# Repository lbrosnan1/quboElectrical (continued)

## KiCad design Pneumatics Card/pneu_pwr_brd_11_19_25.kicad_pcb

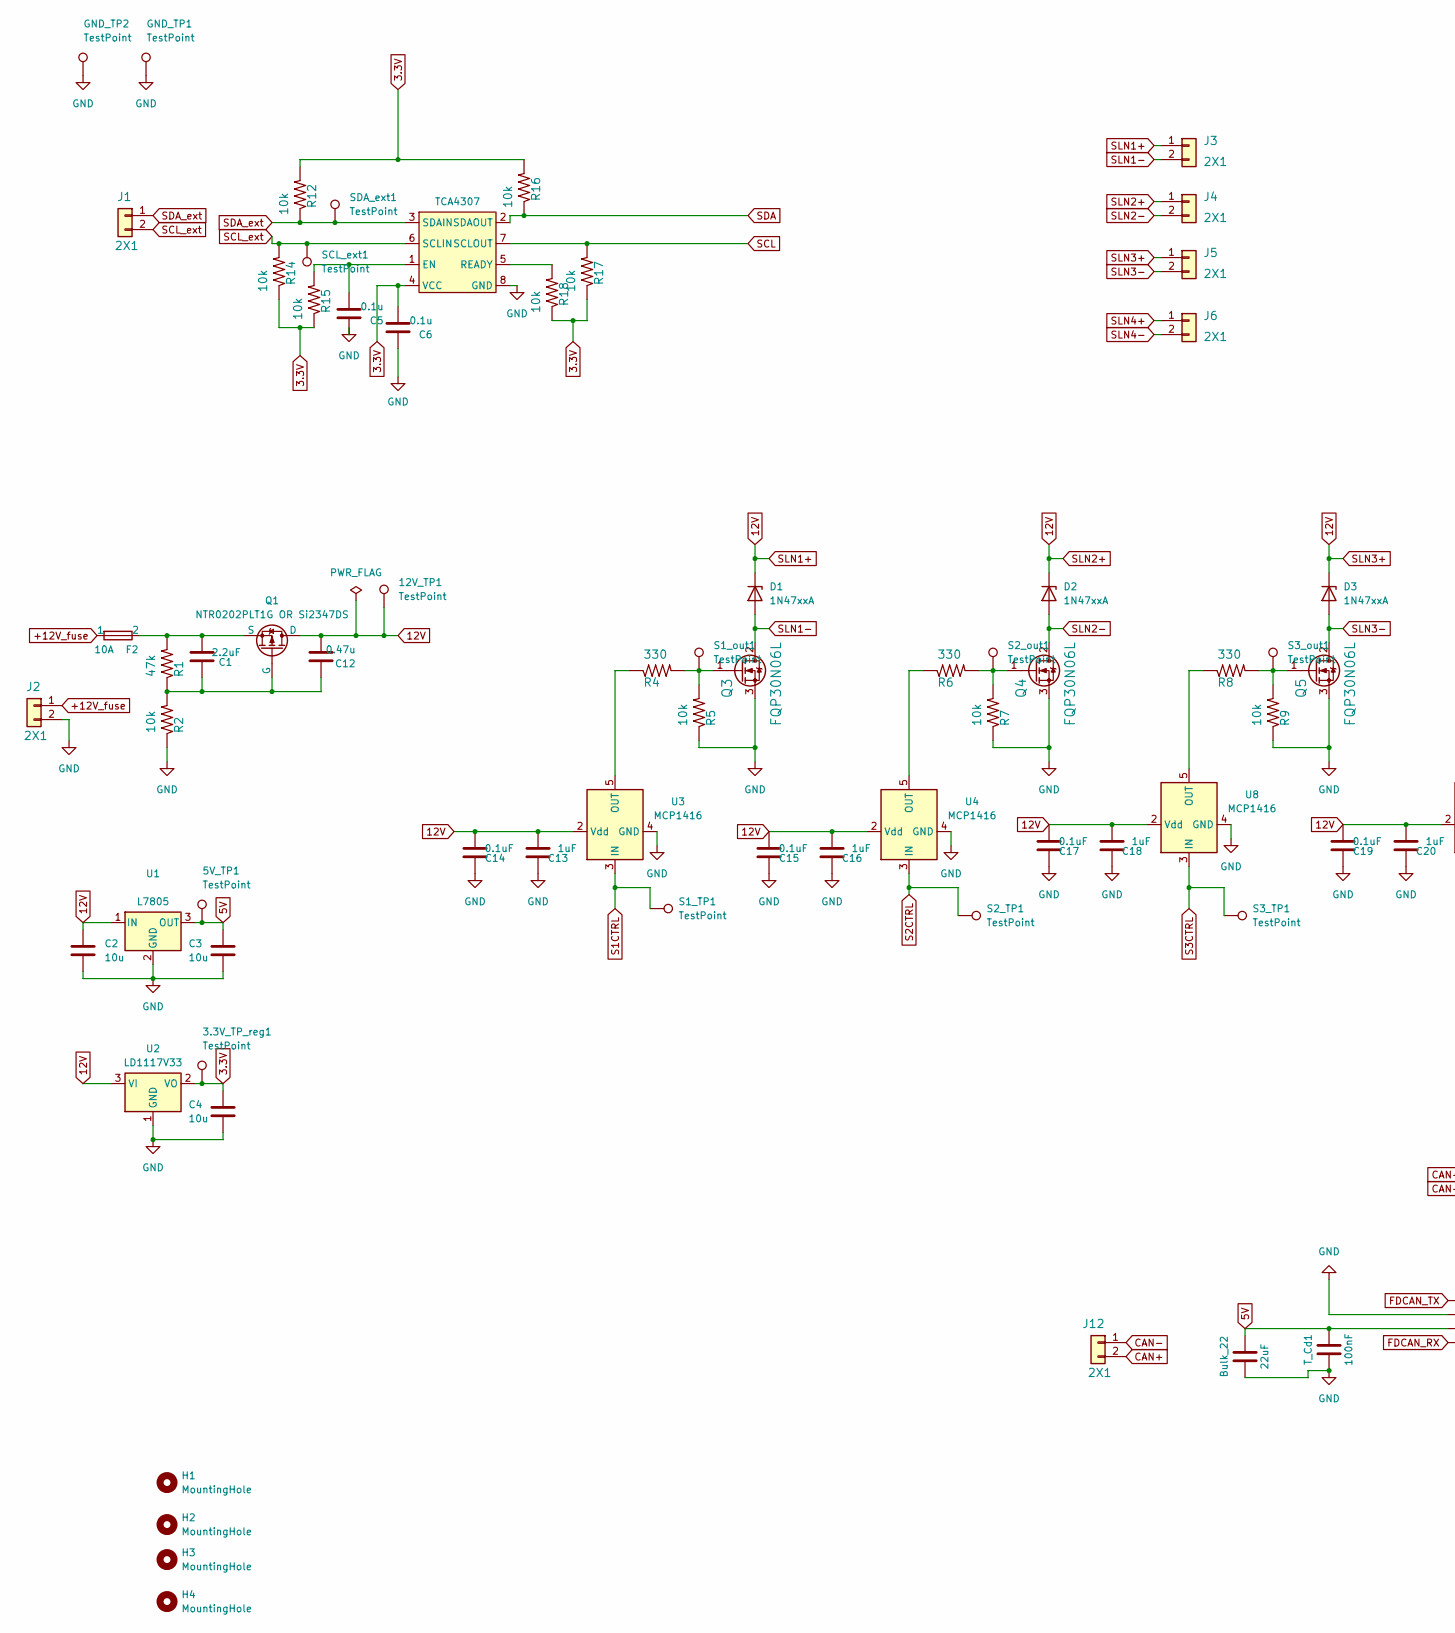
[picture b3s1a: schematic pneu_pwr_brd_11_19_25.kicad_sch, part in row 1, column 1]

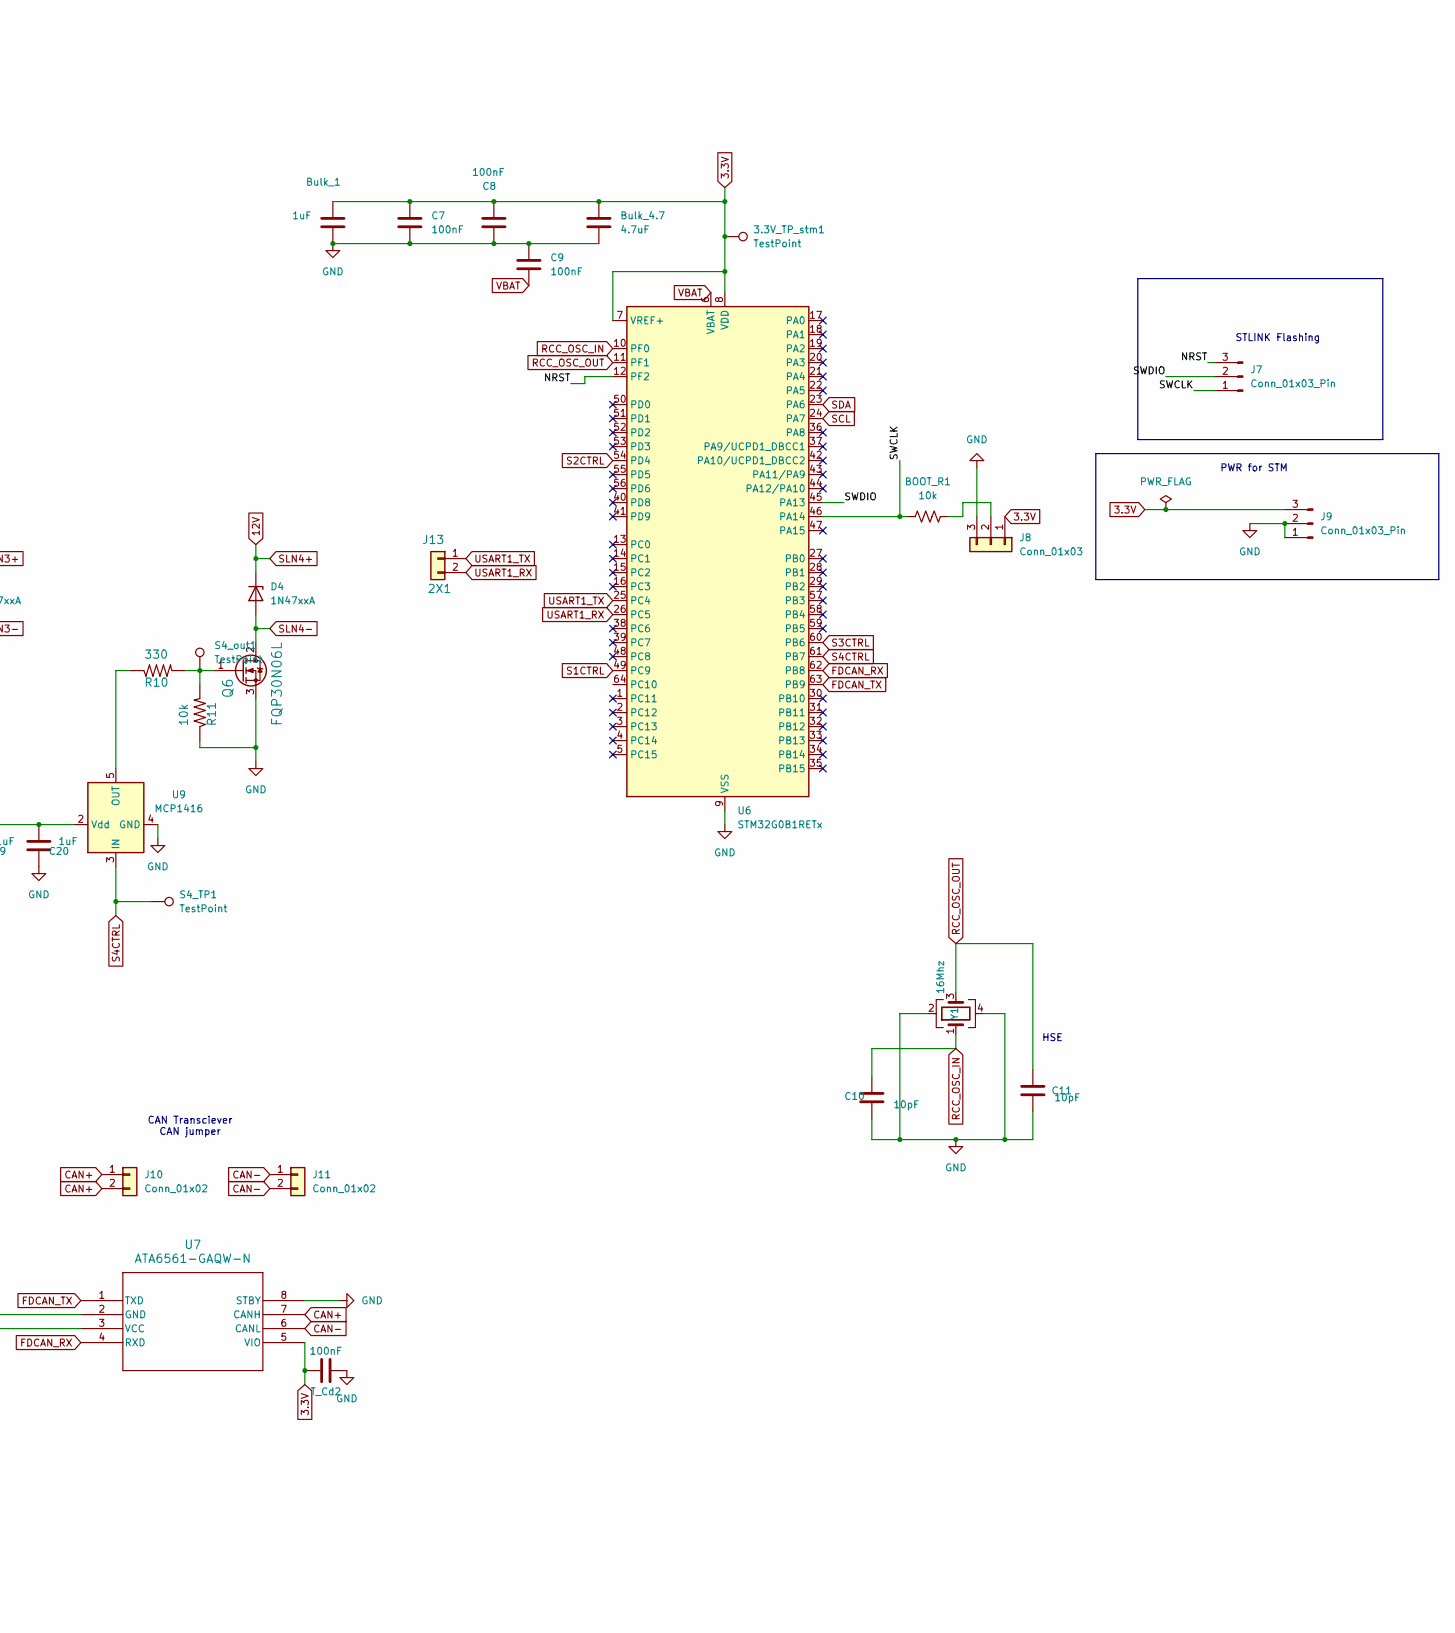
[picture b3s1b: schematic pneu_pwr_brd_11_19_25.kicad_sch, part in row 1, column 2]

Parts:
3.3V_TP_reg1, 3.3V_TP_stm1, 5V_TP1, 12V_TP1: TestPoint; PinHeader_1x01_P1.00mm_Vertical
BOOT_R1: 10k; R_0805_2012Metric_Pad1.20x1.40mm_HandSolder
Bulk_1: 1uF; C_0805_2012Metric_Pad1.18x1.45mm_HandSolder
Bulk_4.7: 4.7uF; C_0805_2012Metric_Pad1.18x1.45mm_HandSolder
Bulk_22: 22uF; C_0805_2012Metric_Pad1.18x1.45mm_HandSolder
C1: 2.2uF; C_0402_1005Metric
C2, C3, C4: 10u; CP_Radial_D5.0mm_P2.00mm
C5, C6: 0.1u; C_0603_1608Metric
C7, C8, C9: 100nF; C_0805_2012Metric_Pad1.18x1.45mm_HandSolder
C10, C11: 10pF; C_0402_1005Metric_Pad0.74x0.62mm_HandSolder
C12: 0.47u; C_0402_1005Metric
C13, C16, C18, C20: 1uF; C_0402_1005Metric
C14, C15, C17, C19: 0.1uF; C_0402_1005Metric
D1, D2, D3, D4: 1N47xxA; D_DO-41_SOD81_P10.16mm_Horizontal
F2: 10A; Fuse_1206_3216Metric
GND_TP1, GND_TP2: TestPoint; PinHeader_1x01_P1.00mm_Vertical
H1, H2, H3, H4: MountingHole; MountingHole_3.2mm_M3_DIN965
J1, J2, J3, J4, J5, J6, J12, J13: 2X1; JST_PH_B2B-PH-K_1x02_P2.00mm_Vertical
J7, J9: Conn_01x03_Pin; PinHeader_1x03_P2.54mm_Vertical
J8: Conn_01x03; slide_switch_EGER1218_Thruster
J10, J11: Conn_01x02; PinHeader_1x02_P2.54mm_Vertical
Q1: NTR0202PLT1G OR Si2347DS; SOT-23-3
Q3, Q4, Q5, Q6: FQP30N06L; TO-220-3_Vertical
R1: 47k; R_0402_1005Metric
R2: 10k; R_0402_1005Metric
R4, R6, R8, R10: 330; R_0805_2012Metric_Pad1.20x1.40mm_HandSolder
R5, R7, R9, R11: 10k; R_0805_2012Metric_Pad1.20x1.40mm_HandSolder
R12, R14, R15, R16, R17, R18: 10k; R_0603_1608Metric
S1_TP1, S1_out1, S2_TP1, S2_out1, S3_TP1, S3_out1, S4_TP1, S4_out1: TestPoint; PinHeader_1x01_P1.00mm_Vertical
SCL_ext1: TestPoint; PinHeader_1x01_P1.00mm_Vertical
SDA_ext1: TestPoint; PinHeader_1x01_P1.00mm_Vertical
T_Cd1, T_Cd2: 100nF; C_0805_2012Metric_Pad1.18x1.45mm_HandSolder
U1: L7805; TO-220-3_Vertical
U2: LD1117V33; TO-220-3_Vertical
U3, U4, U8, U9: MCP1416; SOT-23-5
U5: TCA4307; SOIC8_DGK_TEX
U6: STM32G0B1RETx; LQFP-64_10x10mm_P0.5mm
U7: ATA6561-GAQW-N; SOIC8_4P9X3P9MC_MCH
Y1: 16Mhz; Crystal_SMD_3225-4Pin_3.2x2.5mm

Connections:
3.3V: 3.3V_TP_reg1.1, 3.3V_TP_stm1.1, Bulk_1.2, Bulk_4.7.1, C4.1, C6.2, C7.1, C8.1, J8.1, J9.3, R12.2, R14.1, R15.1, R16.2, R17.1, R18.1, T_Cd2.1, U2.2 (VO), U5.4 (VCC), U6.7 (VREF+), U6.8 (VDD), U7.5 (VIO)
5V: 5V_TP1.1, Bulk_22.1, C3.1, T_Cd1.1, U1.3 (OUT), U7.3 (VCC)
12V: 12V_TP1.1, C2.1, C12.2, C13.2, C14.2, C15.2, C16.2, C17.2, C18.2, C19.2, C20.2, D1.1 (K), D2.1 (K), D3.1 (K), D4.1 (K), J3.1, J4.1, J5.1, J6.1, Q1.1 (D), U1.1 (IN), U2.3 (VI), U3.2 (Vdd), U4.2 (Vdd), U8.2 (Vdd), U9.2 (Vdd)
+12V_fuse: F2.1, J2.1
/NRST: J7.3, U6.12 (PF2)
/SWCLK: BOOT_R1.1, J7.1, U6.46 (PA14)
/SWDIO: J7.2, U6.45 (PA13)
CAN+: J10.1, J10.2, J12.2, U7.7 (CANH)
CAN-: J11.1, J11.2, J12.1, U7.6 (CANL)
FDCAN_RX: U6.62 (PB8), U7.4 (RXD)
FDCAN_TX: U6.63 (PB9), U7.1 (TXD)
GND: Bulk_1.1, Bulk_4.7.2, Bulk_22.2, C2.2, C3.2, C4.2, C5.1, C6.1, C7.2, C8.2, C9.1, C10.2, C11.2, C13.1, C14.1, C15.1, C16.1, C17.1, C18.1, C19.1, C20.1, GND_TP1.1, GND_TP2.1, J2.2, J8.3, J9.1, J9.2, Q3.3 (S), Q4.3 (S), Q5.3 (S), Q6.3 (S), R2.1, R5.1, R7.1, R9.1, R11.1, T_Cd1.2, T_Cd2.2, U1.2 (GND), U2.1 (GND), U3.4 (GND), U4.4 (GND), U5.8 (GND), U6.9 (VSS), U7.2 (GND), U7.8 (STBY), U8.4 (GND), U9.4 (GND), Y1.2, Y1.4
unnamed: BOOT_R1.2, J8.2
unnamed: C1.1, C12.1, Q1.2 (G), R1.1, R2.2
unnamed: C1.2, F2.2, Q1.3 (S), R1.2
unnamed: Q3.1 (G), R4.2, R5.2, S1_out1.1
unnamed: Q4.1 (G), R6.2, R7.2, S2_out1.1
unnamed: Q5.1 (G), R8.2, R9.2, S3_out1.1
unnamed: Q6.1 (G), R10.2, R11.2, S4_out1.1
unnamed: R4.1, U3.5 (OUT)
unnamed: R6.1, U4.5 (OUT)
unnamed: C5.2, R15.2, U5.1 (EN)
unnamed: R18.2, U5.5 (READY)
unnamed: R8.1, U8.5 (OUT)
unnamed: R10.1, U9.5 (OUT)
RCC_OSC_IN: C10.1, U6.10 (PF0), Y1.1
RCC_OSC_OUT: C11.1, U6.11 (PF1), Y1.3
S1CTRL: S1_TP1.1, U3.3 (IN), U6.49 (PC9)
S2CTRL: S2_TP1.1, U4.3 (IN), U6.54 (PD4)
S3CTRL: S3_TP1.1, U6.60 (PB6), U8.3 (IN)
S4CTRL: S4_TP1.1, U6.61 (PB7), U9.3 (IN)
SCL: R17.2, U5.7 (SCLOUT), U6.24 (PA7)
SCL_ext: J1.2, R14.2, SCL_ext1.1, U5.6 (SCLIN); also elsewhere on the board
SDA: R16.1, U5.2 (SDAOUT), U6.23 (PA6)
SDA_ext: J1.1, R12.1, SDA_ext1.1, U5.3 (SDAIN); also elsewhere on the board
SLN1-: D1.2 (A), J3.2, Q3.2 (D)
SLN2-: D2.2 (A), J4.2, Q4.2 (D)
SLN3-: D3.2 (A), J5.2, Q5.2 (D)
SLN4-: D4.2 (A), J6.2, Q6.2 (D)
USART1_RX: J13.2, U6.26 (PC5)
USART1_TX: J13.1, U6.25 (PC4)
VBAT: C9.2, U6.6 (VBAT)

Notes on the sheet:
HSE
STLINK Flashing
CAN Transciever CAN jumper
PWR for STM

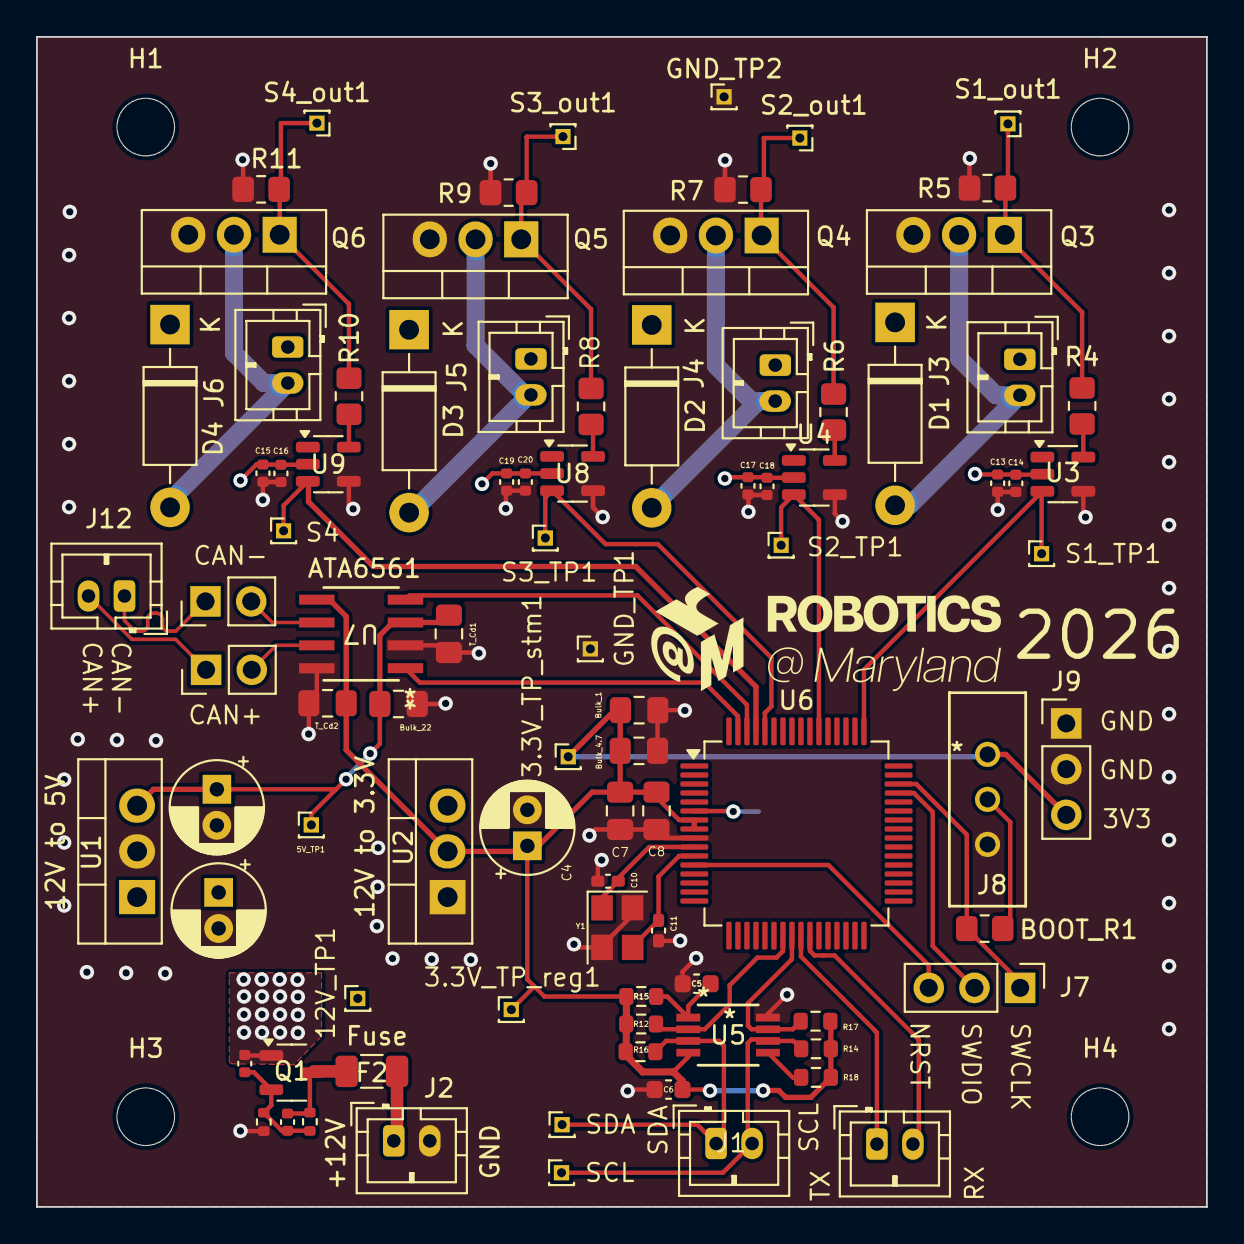
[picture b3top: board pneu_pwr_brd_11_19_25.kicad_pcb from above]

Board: 4 copper layers, 65.0 x 65.0 mm, 95 parts (1 on the bottom side), 42 nets.

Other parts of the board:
SCL: TestPoint; PinHeader_1x01_P1.00mm_Vertical
SDA: TestPoint; PinHeader_1x01_P1.00mm_Vertical

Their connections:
SCL_ext: SCL.1; also elsewhere on the board
SDA_ext: SDA.1; also elsewhere on the board

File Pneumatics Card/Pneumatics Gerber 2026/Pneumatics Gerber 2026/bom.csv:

Designator,Footprint,Quantity,Value,LCSC Part #
"12V_TP1, 3.3V_TP_REG1, 3.3V_TP_STM1, 5V_TP1, GND_TP1, GND_TP2, S1_OUT1, S1_TP1, S2_OUT1, S2_TP1, S3_OUT1, S3_TP1, S4_OUT1, S4_TP1, SCL, SDA",PinHeader_1x01_P1.00mm_Vertical,16,TestPoint,
"BOOT_R1, R11, R5, R7, R9",0805,5,10k,
BULK_1,0805,1,1uF,
BULK_22,0805,1,22uF,
BULK_4.7,0805,1,4.7uF,
C1,0402,1,2.2uF,
"C10, C11",0402,2,10pF,
C12,0402,1,0.47u,
"C13, C16, C18, C20",0402,4,1uF,
"C14, C15, C17, C19",0402,4,0.1uF,
"C2, C3, C4",CP_Radial_D5.0mm_P2.00mm,3,10u,
"C5, C6",0603,2,0.1u,
"C7, C8, C9, T_CD1, T_CD2",0805,5,100nF,
"D1, D2, D3, D4",D_DO-41_SOD81_P10.16mm_Horizontal,4,1N47xxA,
F2,1206,1,10A,
"J1, J12, J13, J2, J3, J4, J5, J6",JST_PH_B2B-PH-K_1x02_P2.00mm_Vertical,8,2X1,
"J10, J11",PinHeader_1x02_P2.54mm_Vertical,2,Conn_01x02,
"J7, J9",PinHeader_1x03_P2.54mm_Vertical,2,Conn_01x03_Pin,
J8,slide_switch_EGER1218_Thruster,1,Conn_01x03,
Q1,SOT-23-3,1,NTR0202PLT1G OR Si2347DS,
"Q3, Q4, Q5, Q6",TO-220-3_Vertical,4,FQP30N06L,
R1,0402,1,47k,
"R10, R4, R6, R8",0805,4,330,
"R12, R14, R15, R16, R17, R18",0603,6,10k,
R2,0402,1,10k,
U1,TO-220-3_Vertical,1,L7805,
U2,TO-220-3_Vertical,1,LD1117V33,
"U3, U4, U8, U9",SOT-23-5,4,MCP1416,
U5,SOIC8_DGK_TEX,1,TCA4307,
U6,LQFP-64_10x10mm_P0.5mm,1,STM32G0B1RETx,
U7,SOIC8_4P9X3P9MC_MCH,1,ATA6561-GAQW-N,
Y1,Crystal_SMD_3225-4Pin_3.2x2.5mm,1,16Mhz,

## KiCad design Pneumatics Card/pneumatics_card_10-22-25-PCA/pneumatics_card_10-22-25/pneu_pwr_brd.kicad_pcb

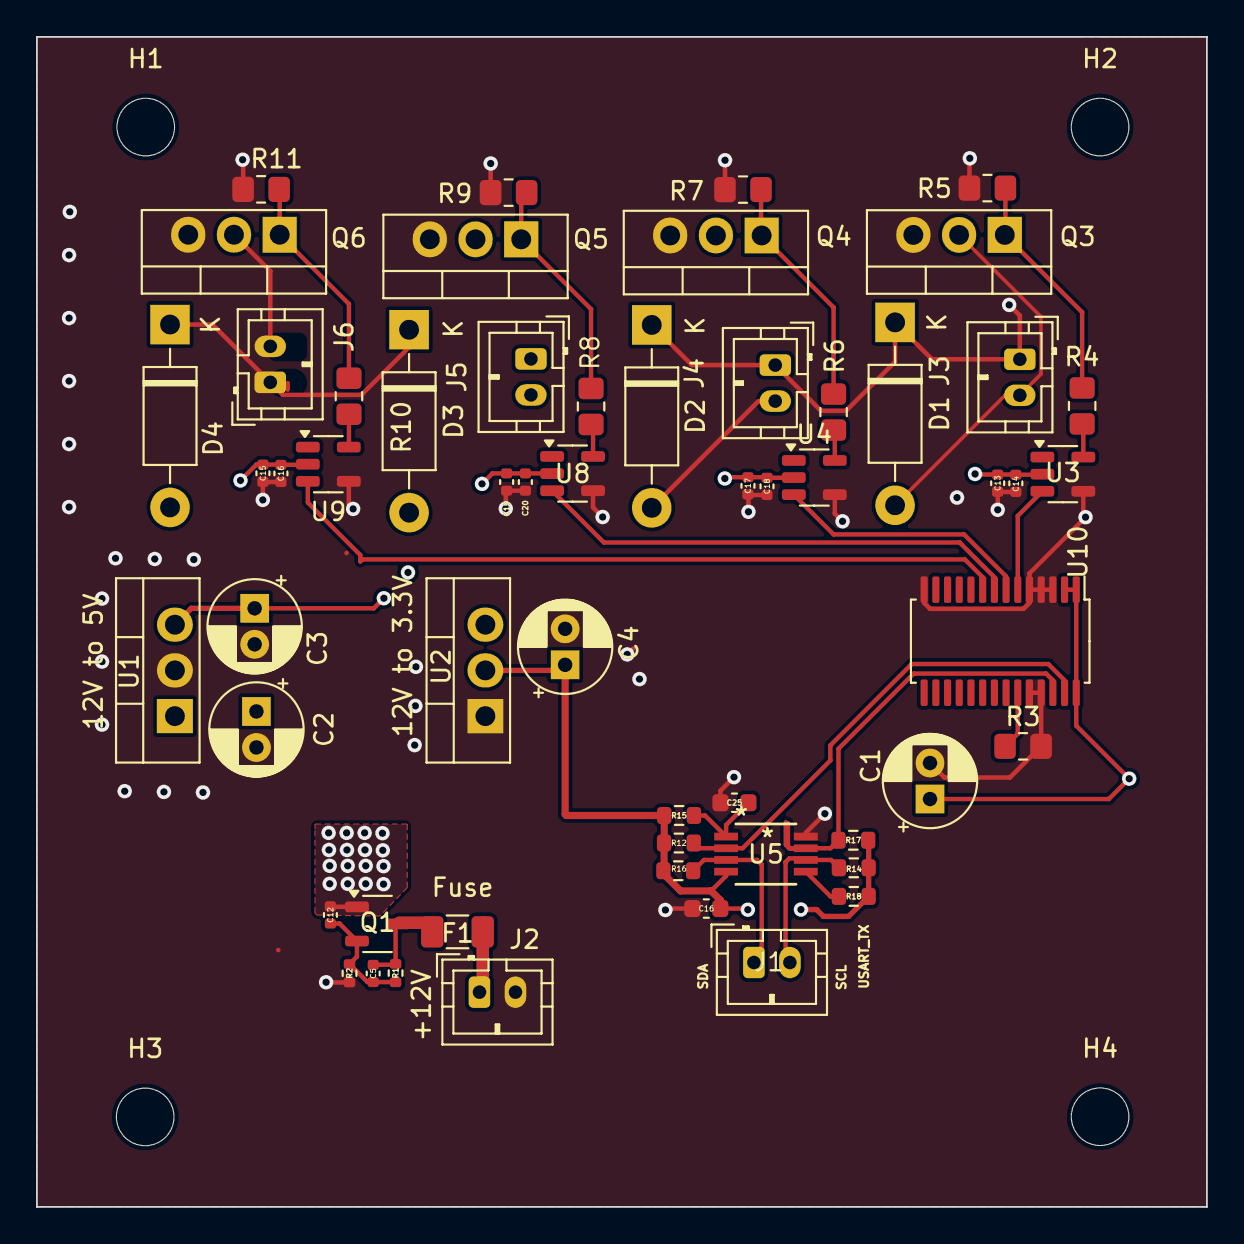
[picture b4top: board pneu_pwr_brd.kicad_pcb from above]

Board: 2 copper layers, 65.0 x 65.0 mm, 61 parts (0 on the bottom side), 31 nets.

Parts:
C1, C2, C3, C4: 10u; CP_Radial_D5.0mm_P2.00mm
C5: 22nF; C_0402_1005Metric
C12: 0.47u; C_0402_1005Metric
C13, C16, C18, C20: 1uF; C_0402_1005Metric
C14, C15, C17, C19: 0.1uF; C_0402_1005Metric
C16#2, C25: 0.1u; C_0603_1608Metric
D1, D2, D3, D4: 1N47xxA; D_DO-41_SOD81_P10.16mm_Horizontal
F1: 10A; Fuse_1206_3216Metric
H1, H2, H3, H4: MountingHole; MountingHole_3.2mm_M3_DIN965
J1, J2, J3, J4, J5, J6: 2X1; JST_PH_B2B-PH-K_1x02_P2.00mm_Vertical
Q1: NTR0202PLT1G OR Si2347DS; SOT-23-3
Q3, Q4, Q5, Q6: FQP30N06L; TO-220-3_Vertical
R1: 1k; R_0402_1005Metric
R2: 4.7k; R_0402_1005Metric
R3, R5, R7, R9, R11: 10k; R_0805_2012Metric_Pad1.20x1.40mm_HandSolder
R4, R6, R8, R10: 330; R_0805_2012Metric_Pad1.20x1.40mm_HandSolder
R12, R14, R15, R16, R17, R18: 10k; R_0603_1608Metric
U1: L7805; TO-220-3_Vertical
U2: LD1117V33; TO-220-3_Vertical
U3, U4, U8, U9: MCP1416; SOT-23-5
U5: TCA4307; SOIC8_DGK_TEX
U10: PCA9685; TSSOP-28_4.4x9.7mm_P0.65mm

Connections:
3.3V: C4.1, C16#2.2, R12.2, R14.1, R15.1, R16.2, R17.1, R18.1, U2.2 (VO), U5.4 (VCC)
5V: C3.1, U1.3 (OUT)
12V: C2.1, C12.2, C13.2, C14.2, C15.2, C16.2, C17.2, C18.2, C19.2, C20.2, D1.1 (K), D2.1 (K), D3.1 (K), D4.1 (K), J3.1, J4.1, J5.1, J6.1, Q1.1 (D), U1.1 (IN), U2.3 (VI), U3.2 (Vdd), U4.2 (Vdd), U8.2 (Vdd), U9.2 (Vdd)
+5V: C1.1, U10.1 (A0), U10.2 (A1), U10.28 (VDD)
+12V_fuse: F1.1, J2.1
GND: C1.2, C2.2, C3.2, C4.2, C13.1, C14.1, C15.1, C16.1, C16#2.1, C17.1, C18.1, C19.1, C20.1, C25.1, J2.2, Q3.3 (S), Q4.3 (S), Q5.3 (S), Q6.3 (S), R2.1, R3.2, R5.1, R7.1, R9.1, R11.1, U1.2 (GND), U2.1 (GND), U3.4 (GND), U4.4 (GND), U5.8 (GND), U8.4 (GND), U9.4 (GND), U10.3 (A2), U10.4 (A3), U10.5 (A4), U10.14 (GND), U10.24 (A5), U10.25 (EXTCLK)
unnamed: C5.1, C12.1, Q1.2 (G), R1.1, R2.2
unnamed: C5.2, F1.2, Q1.3 (S), R1.2
unnamed: Q3.1 (G), R4.2, R5.2
unnamed: Q4.1 (G), R6.2, R7.2
unnamed: Q5.1 (G), R8.2, R9.2
unnamed: Q6.1 (G), R10.2, R11.2
unnamed: R3.1, U10.23 (OE')
unnamed: R4.1, U3.5 (OUT)
unnamed: R6.1, U4.5 (OUT)
unnamed: C25.2, R15.2, U5.1 (EN)
unnamed: R18.2, U5.5 (READY)
unnamed: R8.1, U8.5 (OUT)
unnamed: R10.1, U9.5 (OUT)
S1CTRL: U3.3 (IN), U10.6 (PWM0)
S2CTRL: U4.3 (IN), U10.7 (PWM1)
S3CTRL: U8.3 (IN), U10.8 (PWM2)
S4CTRL: U9.3 (IN), U10.9 (PWM3)
SCL: R17.2, U5.7 (SCLOUT), U10.26 (SCL)
SCL_ext: J1.2, R14.2, U5.6 (SCLIN)
SDA: R16.1, U5.2 (SDAOUT), U10.27 (SDA)
SDA_ext: J1.1, R12.1, U5.3 (SDAIN)
SLN1-: D1.2 (A), J3.2, Q3.2 (D)
SLN2-: D2.2 (A), J4.2, Q4.2 (D)
SLN3-: D3.2 (A), J5.2, Q5.2 (D)
SLN4-: D4.2 (A), J6.2, Q6.2 (D)

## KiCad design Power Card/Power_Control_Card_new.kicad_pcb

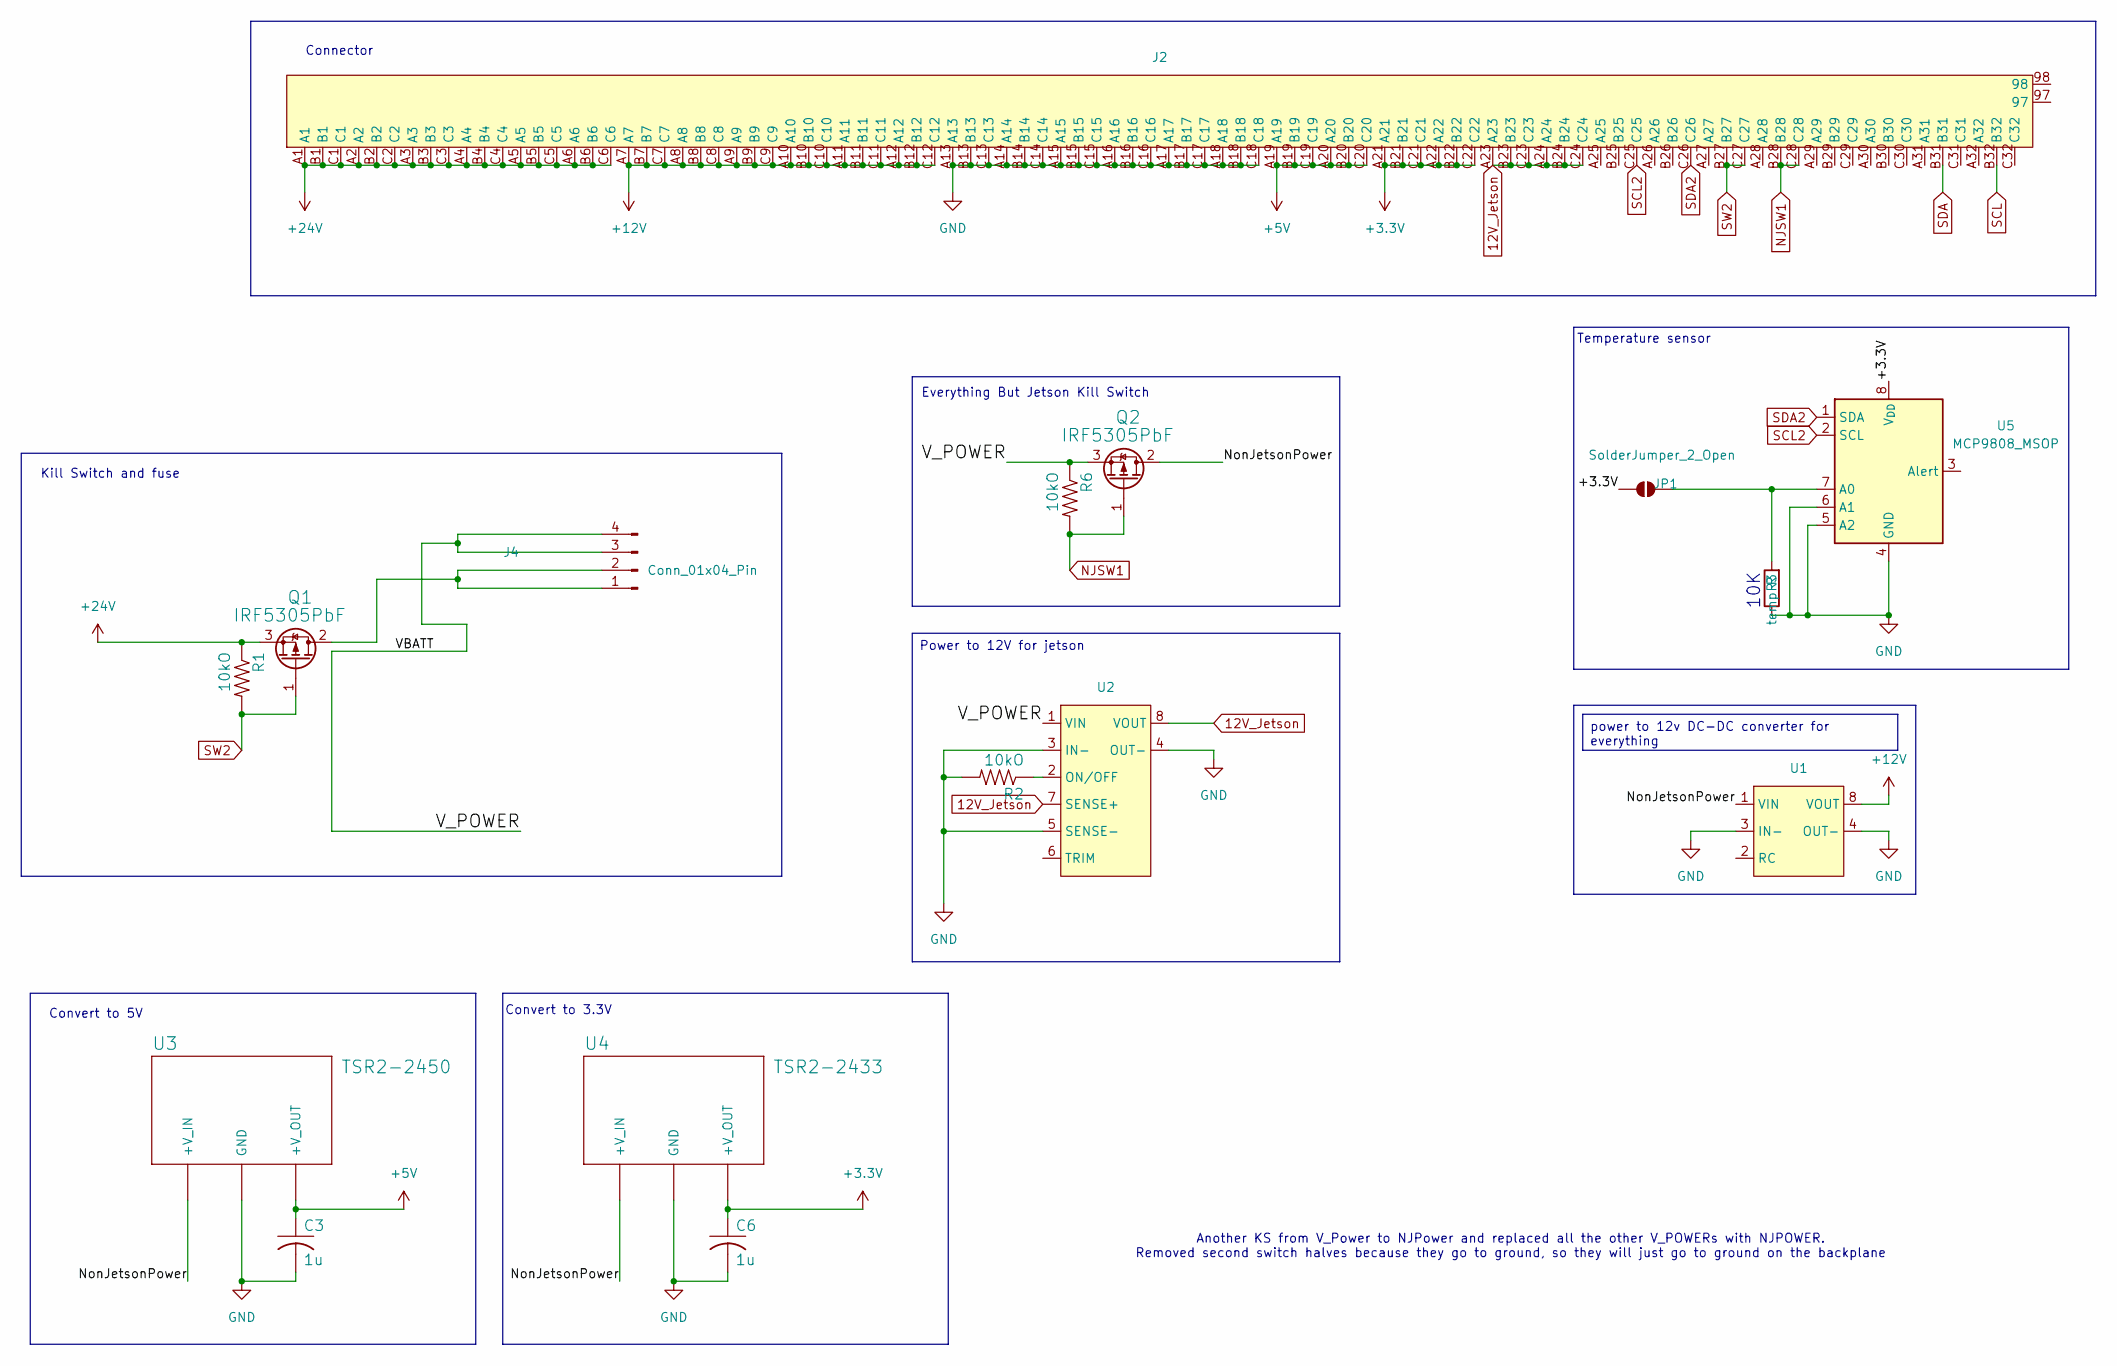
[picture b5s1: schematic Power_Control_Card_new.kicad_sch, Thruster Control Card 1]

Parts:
C3, C6: 1u; C_0805_2012Metric_Pad1.18x1.45mm_HandSolder
J2: 6509475
J4: Conn_01x04_Pin; 1.25__FUSECLIPS
JP1: SolderJumper_2_Open; SolderJumper-2_P1.3mm_Open_RoundedPad1.0x1.5mm
Q1, Q2: IRF5305PbF; TO-220-3_Vertical
R1, R2, R6: 10kO; R_0805_2012Metric_Pad1.20x1.40mm_HandSolder
R3: temp R; R_0805_2012Metric_Pad1.20x1.40mm_HandSolder
U1: 240W_CONV
U2: 72W_CONV
U3: TSR2-2450; TSR2 DC/DC Converter
U4: TSR2-2433; TSR2 DC/DC Converter
U5: MCP9808_MSOP; MSOP-8_3x3mm_P0.65mm

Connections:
12V_Jetson: J2.A23, J2.A24, J2.B23, J2.B24, J2.C23, J2.C24, U2.7 (SENSE+), U2.8 (VOUT)
+3.3V: C6.1, J2.A21, J2.A22, J2.B21, J2.B22, J2.C21, J2.C22, JP1.1 (A), U4.3 (+V_OUT), U5.8 (V_{DD})
+5V: C3.1, J2.A19, J2.A20, J2.B19, J2.B20, J2.C19, J2.C20, U3.3 (+V_OUT)
+12V: J2.A7, J2.A8, J2.A9, J2.A10, J2.A11, J2.A12, J2.B7, J2.B8, J2.B9, J2.B10, J2.B11, J2.B12, J2.C7, J2.C8, J2.C9, J2.C10, J2.C11, J2.C12, U1.8 (VOUT)
+24V: J2.A1, J2.A2, J2.A3, J2.A4, J2.A5, J2.A6, J2.B1, J2.B2, J2.B3, J2.B4, J2.B5, J2.B6, J2.C1, J2.C2, J2.C3, J2.C4, J2.C5, J2.C6, Q1.3 (S), R1.1
/NonJetsonPower: Q2.2 (D), U1.1 (VIN), U3.1 (+V_IN), U4.1 (+V_IN)
/VBATT: J4.3, J4.4, Q2.3 (S), R6.1, U2.1 (VIN)
GND: C3.2, C6.2, J2.A13, J2.A14, J2.A15, J2.A16, J2.A17, J2.A18, J2.B13, J2.B14, J2.B15, J2.B16, J2.B17, J2.B18, J2.C13, J2.C14, J2.C15, J2.C16, J2.C17, J2.C18, R2.2, R3.1, U1.3 (IN-), U1.4 (OUT-), U2.3 (IN-), U2.4 (OUT-), U2.5 (SENSE-), U3.2 (GND), U4.2 (GND), U5.4 (GND), U5.5 (A2), U5.6 (A1); also elsewhere on the board
NJSW1: J2.B28, J2.C28, Q2.1 (G), R6.2; also elsewhere on the board
unnamed: J4.1, J4.2, Q1.2 (D)
unnamed: JP1.2 (B), R3.2, U5.7 (A0)
unnamed: R2.1, U2.2 (ON/OFF)
SCL: J2.B32
SCL2: J2.C25, U5.2 (SCL)
SDA: J2.B31
SDA2: J2.C26, U5.1 (SDA)
SW2: J2.B27, J2.C27, Q1.1 (G), R1.2

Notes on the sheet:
Convert to 3.3V
Kill Switch and fuse
Connector
Temperature sensor
Another KS from V_Power to NJPower and replaced all the other V_POWERs with NJPOWER. Removed second switch halves because they go to ground, so they will just go to ground on the backplane
Convert to 5V
Everything But Jetson Kill Switch
10K
power to 12v DC-DC converter for everything
Power to 12V for jetson

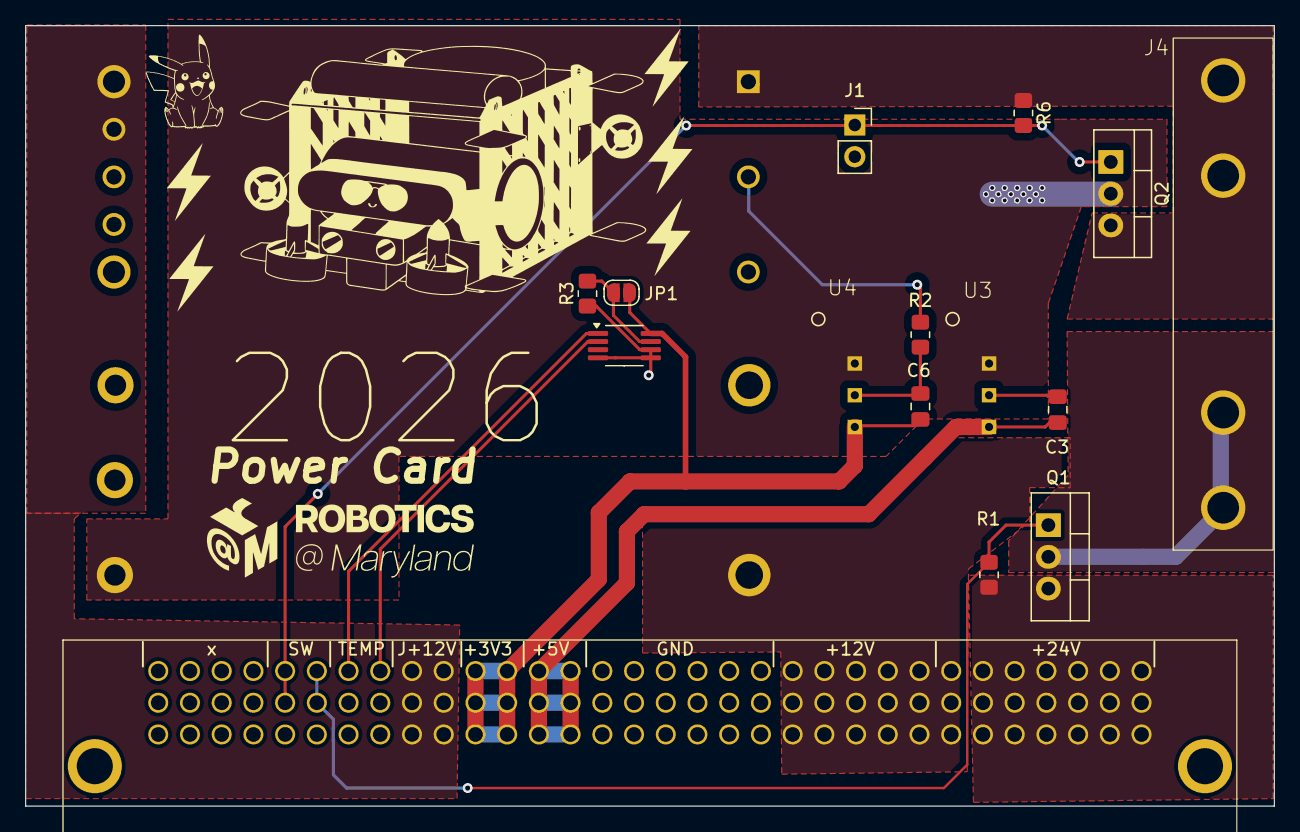
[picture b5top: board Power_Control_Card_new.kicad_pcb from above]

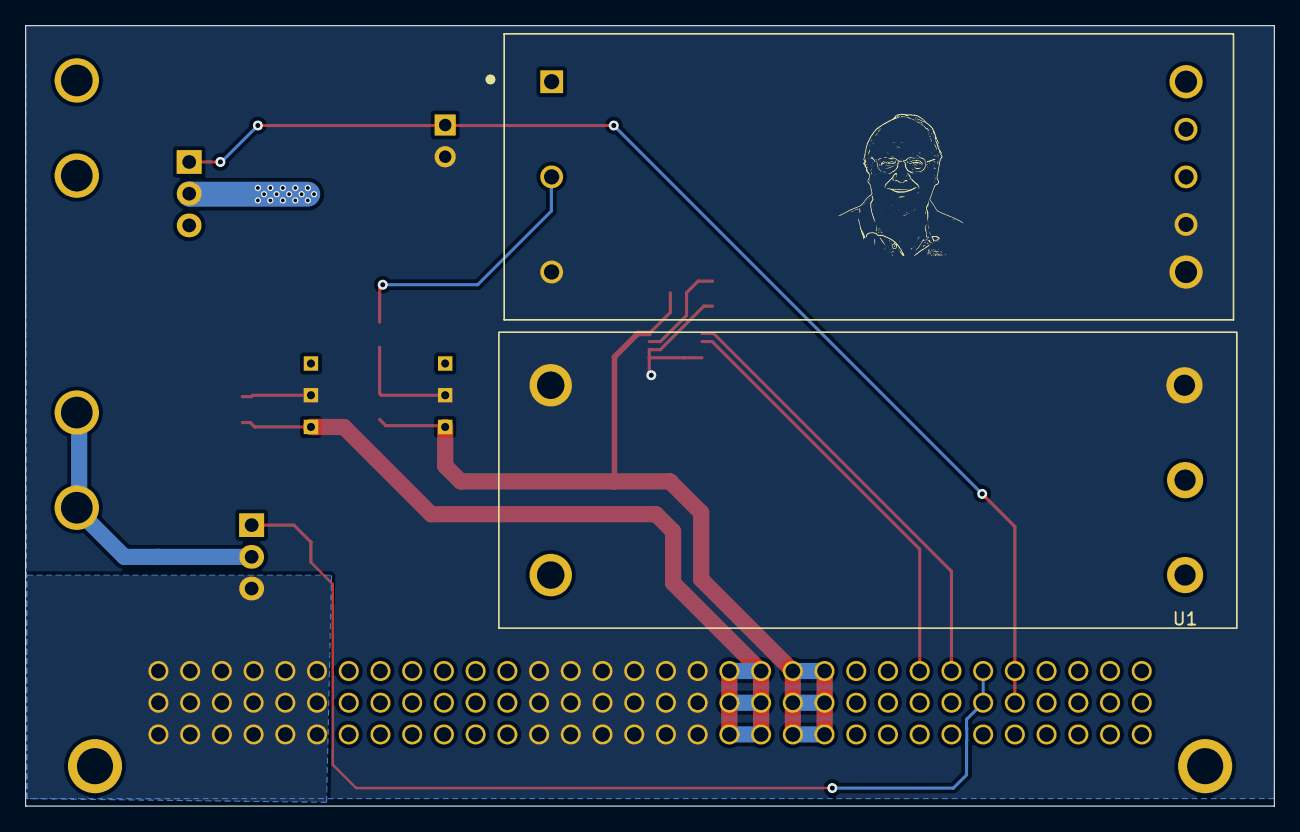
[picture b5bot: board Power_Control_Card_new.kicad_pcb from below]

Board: 2 copper layers, 100.0 x 62.5 mm, 17 parts (2 on the bottom side), 15 nets.

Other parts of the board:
J1: Conn_01x02_Pin; PinSocket_1x02_P2.54mm_Vertical

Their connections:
GND: J1.2; also elsewhere on the board
NJSW1: J1.1; also elsewhere on the board

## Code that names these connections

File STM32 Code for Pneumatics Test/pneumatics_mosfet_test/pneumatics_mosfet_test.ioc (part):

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Mcu.Name=STM32G0B1R(B-C-E)Tx
Mcu.Package=LQFP64
Mcu.UserName=STM32G0B1RETx
PA13.Mode=Serial_Wire
PA13.Signal=SYS_SWDIO
PA14-BOOT0.Mode=Serial_Wire
PA14-BOOT0.Signal=SYS_SWCLK
PA6.Mode=I2C
PA6.Signal=I2C2_SDA
PA7.Mode=I2C
PA7.Signal=I2C2_SCL
PB6.Signal=GPIO_Output
PB7.Signal=GPIO_Output
PC9.Signal=GPIO_Output
PD4.Signal=GPIO_Output
PF0-OSC_IN\ (PF0).Mode=HSE-External-Oscillator
PF0-OSC_IN\ (PF0).Signal=RCC_OSC_IN
PF1-OSC_OUT\ (PF1).Mode=HSE-External-Oscillator
PF1-OSC_OUT\ (PF1).Signal=RCC_OSC_OUT
RCC.HSE_VALUE=16000000
RCC.SYSCLKFreq_VALUE=16000000
RCC.SYSCLKSource=RCC_SYSCLKSOURCE_HSE
board=custom

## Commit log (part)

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2025-11-22 Added Power Card
2025-11-22 Added empty folders for other cards and a readme
2025-11-22 Added Backplane
2025-11-22 Added Thruster Card
2025-11-22 Added Pneumatics Card
2025-11-22 removed folder nest
2025-11-22 Removed Pneumatics Card Backups
2025-11-22 Added Misc Card
2025-11-22 Added BMS
2025-11-22 testing some stuff
2025-11-22 test msg
2025-11-23 idk tbh
2025-11-23 Changed Backplane and Power Card for proper connection between the killswitches in the new system
2025-11-23 Idk what this is but after i closed the files some binary files changed
2025-11-23 testing
2025-11-23 Testing_Anthony
2025-11-24 Added the Mosfet drivers
2025-11-24 Redid the Layout with new components
    Increased board size to 63x63mm, added mounting holes (need to recheck), traces not routed yet.
2025-11-24 Moved the I2C protection for better tracing
2025-11-25 Fixed the footprints and silkscreens
2025-11-29 Made most of routing
2025-12-01 Finished Tracing
    Added USART, Mounting Hole, Stiching Vias, Proper 12V connection.
2025-12-01 Made no change, but GitHub wants me to commit. idk
2025-12-01 Integrated Mounting Holes and made PCB 65x65
2025-12-01 I just opened the files and Git wants me to commit. idk
2025-12-01 Changed some Silk-screen and measured hole size
2025-12-03 Ramp rate values
2025-12-07 Change the M3 hole
2025-12-07 Added more vias to 12V and GND plane
2025-12-07 No change, just commit
2026-01-14 added and fix temp sensor and error
2026-02-05 actually connected the njsw1 resistor
2026-02-08 Added old pneumatics card for back up
2026-02-08 added inrush protection to old pneumatics board
2026-02-08 Added short on power card and fixed some connections
2026-02-08 2nd Kill switch short and fixed connections
2026-02-08 fixed footprint for old pneumatics card
2026-02-08 NJKS short
2026-02-08 PCB for old pneumatics card
2026-02-08 tesitng
2026-02-08 annotating schematic
2026-02-08 old pneumatics fixing PCB
2026-02-08 Corrected CANBUS routing Length.
2026-02-08 added inrush protection to pcb
2026-02-12 old pneumatics
2026-02-12 old pneumatics added mounting holes
2026-02-12 Fixed the i2c line
2026-02-12 routed pneumatics pcb
2026-02-12 finished back up pneumatics
2026-02-15 Changed resistor values
2026-02-22 Put Back up pneumatics board in proper location
2026-03-01 fixed the traces, added test point, fixed some silkscreen
2026-03-01 Fixed test points 3-1-2026
2026-03-08 test point checked
2026-03-08 fixed edge cuts
2026-03-08 Added R@M Silkscreen
2026-03-21 Created Production Files, Sized Up Silkscreen
    Pneumatics Gerber 2026 is the zip file used in the order. I will clean up the other ones later.
2026-03-22 3_22_initiating
2026-03-22 no change
2026-04-15 Uploaded misc board from 4/15/2026
2026-04-19 Added stm32 test code
    Code for testing pneumatics.
    TEST1 and TEST2 in 1 script but PWM Test is on the second folder.
2026-04-22 Added CAN Impedance Matching
    Misc Card
2026-04-22 Added Silkscreen & Backplane Integration
2026-04-23 Kurt Changes
2026-04-26 Added More Connectors to Backplane
2026-04-26 Moved I2C Pins for Power Card
2026-05-25 New STEP Models
